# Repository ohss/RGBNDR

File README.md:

# RGBNDR

RGBNDR is a video synthesiser made by circuit bending a VGA test generator. Inspired by [CHA/V by Jonas Bers](https://jonasbers.com/chav/).

RGBNDR is currently a set of two PCB:s. A board for circuit bending a VGA signal and a board for generating nice signals for bending video. It's a modular design so new boards can be easily added later.

Here's some instructions about how to build one. Schematics, eagle files and gerbers for manufacturing can be found form [https://github.com/ohss/RGBNDR](https://github.com/ohss/RGBNDR)

You can find some examples about what you can do with one on Instagram: [https://www.instagram.com/explore/tags/rgbndr/](https://www.instagram.com/explore/tags/rgbndr/) or you can check out the video below:

# Build it!

You will need to build two boards: RGBNDR board and Modulator board:

Here's a RGBNDR board hooked up to two modulator boards:

Here's a quick tip on how to solder:

## Building RGBNDR (board with VGA test generator)

Here's what you'll need:

| Num | Part | Val | Comment | Link |
|-----|------|-----|---------|------|
|2x1|Male pin header||||			
|3x2|Male pin header||||			
|1x4|Female pin header|90° angle|||
|1|Led|3mm|||
|2|Pushbutton|MOMENTARY-SWITCH-SPST-PTH-6.0MM|||
|5|Slide switch|SLIDE SWITCH 1P2T THROUGH HOLE 0.5A 50VDC||https://www.taydaelectronics.com/slide-switch-1p2t-through-hole-0-5a-50vdc-2713.html|
|3|Ceramic capacitor|0.1uF (104)|Try out different values||
|3|Electrolytic capacitor|10uF|Try out different values. Remember polarity!||
|3|Potentiometer|10k|||
|1|Diode|1N4004|||
|3|Jumper wire||PCB has places for 1N4148 diodes. Use jumpers instead.||
|2|Resistor|1k|||
|1|Transistor|2N2222|Check polarity||
|1|Power Jack||V2 revision has a mistace on power. It's cCenter negative NOT center positive ||	
|3|Mono 3.5mm jack|Thonkiconn|Optional|https://www.thonk.co.uk/shop/3-5mm-jacks/|		

Start with adding caps to the bottom side. Remember to check polarity on electrolytic caps!

Use cap legs that you just cut out as jumpers. You'll need three. On the board there is three spots for 1N4148 diode. Use the jumpers instead.

Add two 1k resistors and 1N4004 diode. Remember to check diode polarity!

Next one is a bit tricky. You'll need to solder header pins to the board. I like to place the header pins on the board, put a piece on cardboard on top of the pins and then flip the whole thing over with the cardboard keeping the pins where they should be. Usually they fall all over the place.

Then: pushbuttons, transistor (match the flat side to the flat line on the board ) and led. Long leg goes to +.

Add female angle header for connecting with other board. Use a helping hand to get the angle header high enough:

Add (in this order): 5 slide switches, power connector, three 3.5mm mono jacks, three 10k potentiometers. For pots and slide switches it's ok to solder only the three middle pins.

Solder wires from the test gen board to the RGBNDR board.

Done!

## Building modulator board

Here's what you'll need:

| Num | Part | Val | Comment | Link |
|-----|------|-----|---------|------|
|11x1|Male pin header||||			
|5x2|Male pin header||||			
|1x4|Male pin header|90° angle|||
|4|LDR||Optional||
|13|Slide switch|SLIDE SWITCH 1P2T THROUGH HOLE 0.5A 50VDC|If you don't use LDRs, replace switch with jumper|https://www.taydaelectronics.com/slide-switch-1p2t-through-hole-0-5a-50vdc-2713.html|
|1|Ceramic capacitor|22pF||||
|1|Ceramic capacitor|0.001uF (102)|||
|2|Ceramic capacitor|0.01uF (103)|||
|5|Ceramic capacitor|0.1uF (104)|||
|2|Electrolytic capacitor|100uF|Remember polarity!||
|1|Electrolytic capacitor|10uF|Remember polarity!||
|1|Electrolytic capacitor|1uF|Remember polarity!||
|6|Potentiometer|100k|||
|1|Resistor|20k|||
|5|Resistor|100R|||
|1|IC|40106|||
|1|IC|4046|||
|1|IC|4070|||

Start with the flattest parts so that soldering is as easy as possible. So:

1. Resistors
2. ICs
3. Header pins
4. Caps
5. Switches
6. LDRs
7. Pots

Few tips:

Use IC sockets and align them correctly. I made a mistake on the photo:

You can chose what ever values for oscillator caps you want. Together with a potentiometer these will define frequency for an oscillator. For each oscillator you can pick big and small cap and change between those with a switch.

My setup is like this but try your own values!

|     |OSC 1|OSC 2|OSC 3|OSC 4|4046 MOD|
|-----|-----|-----|-----|-----|--------|
|SMALL|10nF|0.1nF|0.01nF|0.001nf| - |
| BIG |100nF|1nF|0.1nF|0.01nF|100nF|

I put the big caps on the bottom side.

After some soldering it should look more or less like this:

Hook it up with RGBNDR and that's it!

Later you can make a box for it. Here's an older version with jacks:

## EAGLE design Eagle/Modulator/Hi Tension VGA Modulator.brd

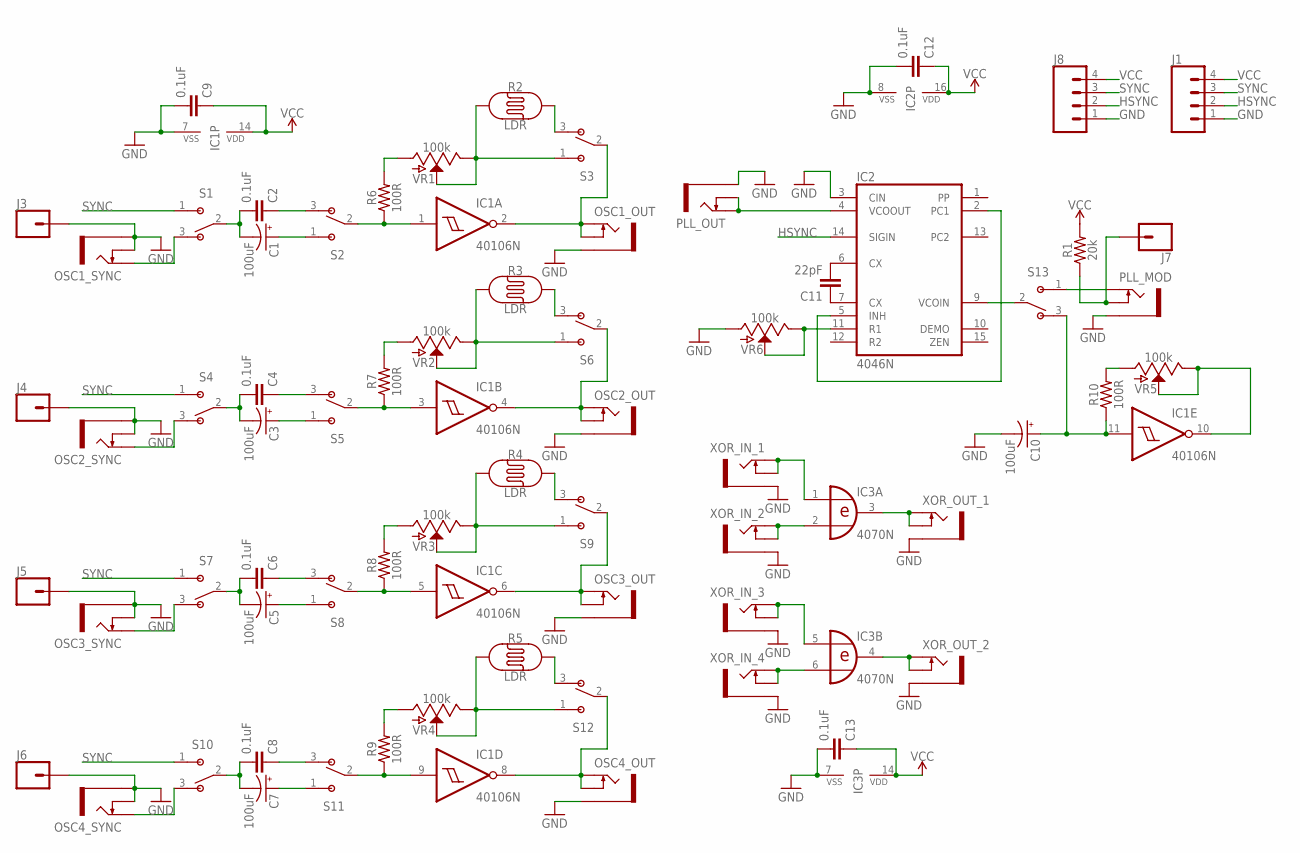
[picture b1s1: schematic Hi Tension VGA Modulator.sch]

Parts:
C1, C3, C5, C7, C10: 100uF; CPOL-RADIAL-2.5MM-6.5MM
C2, C4, C6, C8, C9, C12, C13: 0.1uF; C025-025X050
C11: 22pF; CAP-PTH-2.54
IC1: 40106N; DIL14
IC2: 4046N; DIL16
IC3: 4070N; DIL14
J1, J8: CONN_04; 1X04
J3, J4, J5, J6, J7: CONN_01PTH_NO_SILK_YES_STOP; 1X01_NO_SILK
OSC1_OUT, OSC1_SYNC, OSC2_OUT, OSC2_SYNC, OSC3_OUT, OSC3_SYNC, OSC4_OUT, OSC4_SYNC: THONKICONNNEW; WQP-PJ301M-12_JACK
PLL_MOD: THONKICONNNEW; WQP-PJ301M-12_JACK
PLL_OUT: THONKICONNNEW; WQP-PJ301M-12_JACK
R1: 20k; AXIAL-0.3
R2, R3, R4, R5: LDR; PHOTOCELL
R6, R7, R8, R9, R10: 100R; AXIAL-0.3
S1, S2, S3, S4, S5, S6, S7, S8, S9, S10, S11, S12, S13: OS102011MS2QN1; SW_OS102011MS2QN1
VR1, VR2, VR3, VR4, VR5, VR6: 100k; POT-PTH-ALPS
XOR_IN_1, XOR_IN_2, XOR_IN_3, XOR_IN_4: THONKICONNNEW; WQP-PJ301M-12_JACK
XOR_OUT_1, XOR_OUT_2: THONKICONNNEW; WQP-PJ301M-12_JACK

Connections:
GND: C9.2, C10.2 (-), C12.2, C13.2, IC1.7 (VSS), IC2.3 (CIN), IC2.8 (VSS), IC3.7 (VSS), J1.1, J3.1, J4.1, J5.1, J6.1, J8.1, OSC1_OUT.P$3_SLEEVE (SLEEVE), OSC1_SYNC.P$2_SWITCH (SWITCH), OSC1_SYNC.P$3_SLEEVE (SLEEVE), OSC2_OUT.P$3_SLEEVE (SLEEVE), OSC2_SYNC.P$2_SWITCH (SWITCH), OSC2_SYNC.P$3_SLEEVE (SLEEVE), OSC3_OUT.P$3_SLEEVE (SLEEVE), OSC3_SYNC.P$2_SWITCH (SWITCH), OSC3_SYNC.P$3_SLEEVE (SLEEVE), OSC4_OUT.P$3_SLEEVE (SLEEVE), OSC4_SYNC.P$2_SWITCH (SWITCH), OSC4_SYNC.P$3_SLEEVE (SLEEVE), PLL_MOD.P$3_SLEEVE (SLEEVE), PLL_OUT.P$3_SLEEVE (SLEEVE), VR6.P$3 (A), XOR_IN_1.P$3_SLEEVE (SLEEVE), XOR_IN_2.P$3_SLEEVE (SLEEVE), XOR_IN_3.P$3_SLEEVE (SLEEVE), XOR_IN_4.P$3_SLEEVE (SLEEVE), XOR_OUT_1.P$3_SLEEVE (SLEEVE), XOR_OUT_2.P$3_SLEEVE (SLEEVE)
HSYNC: IC2.14 (SIGIN), J1.2, J8.2
unnamed: OSC1_SYNC.P$1_TIP (TIP), S1.3
unnamed: C1.2 (-), C2.2, S1.2
unnamed: C2.1, S2.3
unnamed: C1.1 (+), S2.1
unnamed: IC1.1 (I), R6.P$1 (1), S2.2
unnamed: R10.P$2 (2), VR5.P$3 (A)
unnamed: R2.1, S3.1, VR1.P$1 (E), VR1.P$2 (S)
unnamed: IC1.2 (O), OSC1_OUT.P$1_TIP (TIP), OSC1_OUT.P$2_SWITCH (SWITCH), S3.2
unnamed: OSC2_SYNC.P$1_TIP (TIP), S4.3
unnamed: C3.2 (-), C4.2, S4.2
unnamed: C3.1 (+), S5.1
unnamed: IC1.3 (I), R7.P$1 (1), S5.2
unnamed: R2.2, S3.3
unnamed: IC1.4 (O), OSC2_OUT.P$1_TIP (TIP), OSC2_OUT.P$2_SWITCH (SWITCH), S6.2
unnamed: C4.1, S5.3
unnamed: OSC3_SYNC.P$1_TIP (TIP), S7.3
unnamed: C5.2 (-), C6.2, S7.2
unnamed: C5.1 (+), S8.1
unnamed: IC1.5 (I), R8.P$1 (1), S8.2
unnamed: R3.2, S6.3
unnamed: R5.2, S12.3
unnamed: IC1.6 (O), OSC3_OUT.P$1_TIP (TIP), OSC3_OUT.P$2_SWITCH (SWITCH), S9.2
unnamed: C6.1, S8.3
unnamed: OSC4_SYNC.P$1_TIP (TIP), S10.3
unnamed: C7.2 (-), C8.2, S10.2
unnamed: C8.1, S11.3
unnamed: IC1.9 (I), R9.P$1 (1), S11.2
unnamed: R4.1, S9.1, VR3.P$1 (E), VR3.P$2 (S)
unnamed: IC1.8 (O), OSC4_OUT.P$1_TIP (TIP), OSC4_OUT.P$2_SWITCH (SWITCH), S12.2
unnamed: C7.1 (+), S11.1
unnamed: C11.1, IC2.7 (CX)
unnamed: C11.2, IC2.6 (CX)
unnamed: IC2.9 (VCOIN), S13.2
unnamed: PLL_MOD.P$1_TIP (TIP), S13.1
unnamed: IC2.2 (PC1), IC2.5 (INH)
unnamed: IC2.4 (VCOOUT), PLL_OUT.P$1_TIP (TIP), PLL_OUT.P$2_SWITCH (SWITCH)
unnamed: J7.1, PLL_MOD.P$2_SWITCH (SWITCH), R1.P$1 (1)
unnamed: C10.1 (+), IC1.11 (I), R10.P$1 (1), S13.3
unnamed: IC1.10 (O), VR5.P$1 (E), VR5.P$2 (S)
unnamed: IC3.5 (I0), XOR_IN_3.P$1_TIP (TIP), XOR_IN_3.P$2_SWITCH (SWITCH)
unnamed: IC2.11 (R1), VR6.P$1 (E), VR6.P$2 (S)
unnamed: IC3.1 (I0), XOR_IN_1.P$1_TIP (TIP), XOR_IN_1.P$2_SWITCH (SWITCH)
unnamed: IC3.2 (I1), XOR_IN_2.P$1_TIP (TIP), XOR_IN_2.P$2_SWITCH (SWITCH)
unnamed: IC3.6 (I1), XOR_IN_4.P$1_TIP (TIP), XOR_IN_4.P$2_SWITCH (SWITCH)
unnamed: IC3.3 (O), XOR_OUT_1.P$1_TIP (TIP), XOR_OUT_1.P$2_SWITCH (SWITCH)
unnamed: IC3.4 (O), XOR_OUT_2.P$1_TIP (TIP), XOR_OUT_2.P$2_SWITCH (SWITCH)
unnamed: R4.2, S9.3
unnamed: R3.1, S6.1, VR2.P$1 (E), VR2.P$2 (S)
unnamed: R5.1, S12.1, VR4.P$1 (E), VR4.P$2 (S)
unnamed: R6.P$2 (2), VR1.P$3 (A)
unnamed: R7.P$2 (2), VR2.P$3 (A)
unnamed: R8.P$2 (2), VR3.P$3 (A)
unnamed: R9.P$2 (2), VR4.P$3 (A)
SYNC: J1.3, J8.3, S1.1, S4.1, S7.1, S10.1
VCC: C9.1, C12.1, C13.1, IC1.14 (VDD), IC2.16 (VDD), IC3.14 (VDD), J1.4, J8.4, R1.P$2 (2)

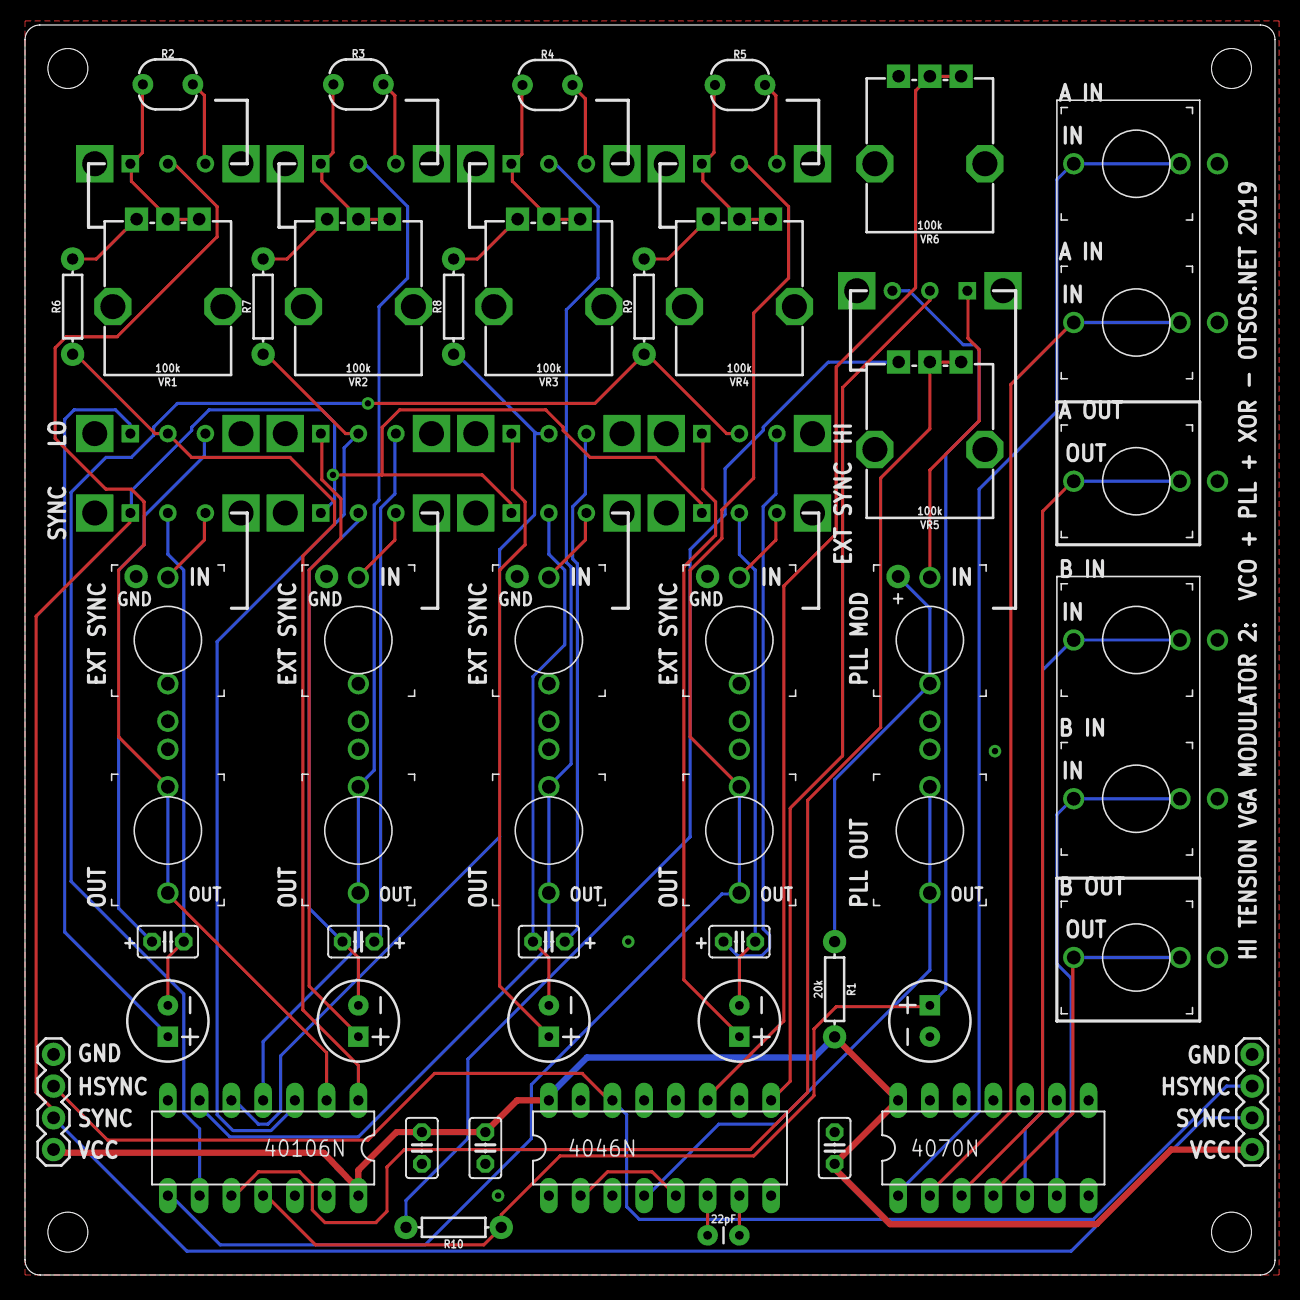
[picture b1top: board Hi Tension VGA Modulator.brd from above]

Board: 2 copper layers, 100.0 x 100.0 mm, 72 parts (0 on the bottom side), 57 nets.

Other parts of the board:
U$1, U$2, U$3, U$4: MOUNTING_HOLE

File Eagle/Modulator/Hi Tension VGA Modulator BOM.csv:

"Qty";"Value";"Device";"Package";"Parts";"Description";"AVAILABILITY";"DESCRIPTION";"MF";"MP";"PACKAGE";"PRICE";"PROD_ID";"SF_ID";"SF_SKU";"SPICEPREFIX";"VALUE";
"5";"";"CONN_01PTH_NO_SILK_YES_STOP";"1X01_NO_SILK";"J3, J4, J5, J6, J7";"Single connection point. Often used as Generic Header-pin footprint for 0.1 inch spaced/style header connections";"";"";"";"";"";"";"";"";"";"";"";
"2";"";"CONN_04";"1X04";"J1, J8";"Multi connection point. Often used as Generic Header-pin footprint for 0.1 inch spaced/style header connections";"";"";"";"";"";"";"CONN-09696";"";"";"";"";
"13";"";"OS102011MS2QN1";"SW_OS102011MS2QN1";"S1, S2, S3, S4, S5, S6, S7, S8, S9, S10, S11, S12, S13";"Switch Slide ON ON SPDT Top Slide 0.1A 12VDC 10000Cycles PC Pins Thru-Hole Bulk";"Unavailable";" Switch Slide ON ON SPDT Top Slide 0.1A 12VDC 10000Cycles PC Pins Thru-Hole Bulk ";"C&K";"OS102011MS2QN1";"DO-201 C&amp";"K Components";"None";"";"";"";"";
"7";"0.1uF";"C-EU025-025X050";"C025-025X050";"C2, C4, C6, C8, C9, C12, C13";"CAPACITOR, European symbol";"";"";"";"";"";"";"";"";"";"C";"";
"5";"100R";"1KOHM-HORIZ-1/4W-1%";"AXIAL-0.3";"R6, R7, R8, R9, R10";"1kΩ resistor";"";"";"";"";"";"";"RES-12182";"";"";"";"1k";
"6";"100k";"POTENTIOMETER-PTH-9MM-1/20W-20%";"POT-PTH-ALPS";"VR1, VR2, VR3, VR4, VR5, VR6";"Potentiometer (Pot)";"";"";"";"";"";"";"RES-09177";"";"COM-09288";"";"10k";
"5";"100uF";"100UF-POLAR-RADIAL-2.5MM-25V-20%";"CPOL-RADIAL-2.5MM-6.5MM";"C1, C3, C5, C7, C10";"100µF polarized capacitors";"";"";"";"";"";"";"CAP-08439";"";"";"";"100uF";
"1";"20k";"1KOHM-HORIZ-1/4W-1%";"AXIAL-0.3";"R1";"1kΩ resistor";"";"";"";"";"";"";"RES-12182";"";"";"";"1k";
"1";"22pF";"22PF-PTH-2.54MM-200V-5%";"CAP-PTH-2.54";"C11";"22pF ceramic capacitors";"";"";"";"";"";"";"CAP-09128";"";"";"";"22pF";
"1";"40106N";"40106N";"DIL14";"IC1";"Hex SCHMITT TRIGGER";"";"";"";"";"";"";"";"";"";"";"";
"1";"4046N";"4046N";"DIL16";"IC2";"Micropower PLL";"";"";"";"";"";"";"";"";"";"";"";
"1";"4070N";"4070N";"DIL14";"IC3";"Quad 2-input XOR";"";"";"";"";"";"";"";"";"";"";"";
"4";"LDR";"PHOTOCELLPTH";"PHOTOCELL";"R2, R3, R4, R5";"Photocell (Photodetector, Photo Resistor, CdS)";"";"";"";"";"";"";"COMP-09129";"SEN-09088";"";"";"";
"16";"THONKICONNNEW";"THONKICONNNEW";"WQP-PJ301M-12_JACK";"OSC1_OUT, OSC1_SYNC, OSC2_OUT, OSC2_SYNC, OSC3_OUT, OSC3_SYNC, OSC4_OUT, OSC4_SYNC, PLL_MOD, PLL_OUT, XOR_IN_1, XOR_IN_2, XOR_IN_3, XOR_IN_4, XOR_OUT_1, XOR_OUT_2";"3.5mm socket for Eurorack modular synths";"";"";"";"";"";"";"";"";"";"";"";

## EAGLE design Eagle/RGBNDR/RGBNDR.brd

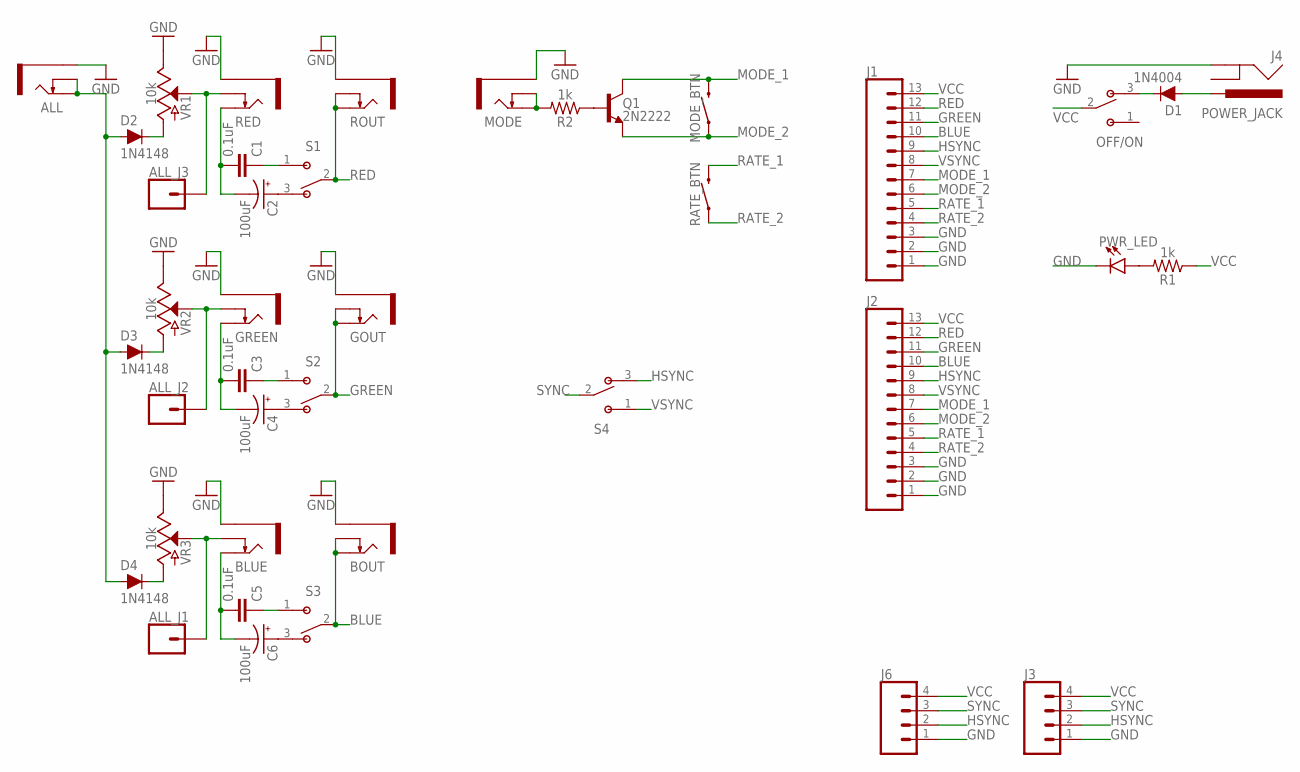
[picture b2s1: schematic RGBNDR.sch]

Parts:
ALL: THONKICONNNEW; WQP-PJ301M-12_JACK
ALL_J1, ALL_J2, ALL_J3: CONN_01PTH_NO_SILK_YES_STOP; 1X01_NO_SILK
BLUE: THONKICONNNEW; WQP-PJ301M-12_JACK
BOUT: THONKICONNNEW; WQP-PJ301M-12_JACK
C1, C3, C5: 0.1uF; C025-025X050
C2, C4, C6: 100uF; CPOL-RADIAL-2.5MM-6.5MM
D1: 1N4004; DIODE-1N4001
D2, D3, D4: 1N4148; DIODE-1N4148
GOUT: THONKICONNNEW; WQP-PJ301M-12_JACK
GREEN: THONKICONNNEW; WQP-PJ301M-12_JACK
J1, J2: CONN_13LONGPADS; 1X13-LONGPADS
J3, J6: CONN_04; 1X04
J4: POWER_JACK; POWER_JACK_PTH
MODE: THONKICONNNEW; WQP-PJ301M-12_JACK
MODE_BTN: MOMENTARY-SWITCH-SPST-PTH-6.0MM; TACTILE_SWITCH_PTH_6.0MM
OFF/ON: OS102011MS2QN1; SW_OS102011MS2QN1
PWR_LED: LED3MM; LED_3MM
Q1: 2N2222; TO-92
R1, R2: 1k; AXIAL-0.3
RATE_BTN: MOMENTARY-SWITCH-SPST-PTH-6.0MM; TACTILE_SWITCH_PTH_6.0MM
RED: THONKICONNNEW; WQP-PJ301M-12_JACK
ROUT: THONKICONNNEW; WQP-PJ301M-12_JACK
S1, S2, S3, S4: OS102011MS2QN1; SW_OS102011MS2QN1
VR1, VR2, VR3: 10k; POT-PTH-ALPS

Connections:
BLUE: BOUT.P$1_TIP (TIP), BOUT.P$2_SWITCH (SWITCH), J1.10, J2.10, S3.2
GND: ALL.P$3_SLEEVE (SLEEVE), BLUE.P$3_SLEEVE (SLEEVE), BOUT.P$3_SLEEVE (SLEEVE), GOUT.P$3_SLEEVE (SLEEVE), GREEN.P$3_SLEEVE (SLEEVE), J1.1, J1.2, J1.3, J2.1, J2.2, J2.3, J3.1, J4.GND, J6.1, MODE.P$3_SLEEVE (SLEEVE), PWR_LED.K (C), RED.P$3_SLEEVE (SLEEVE), ROUT.P$3_SLEEVE (SLEEVE), VR1.P$1 (E), VR2.P$1 (E), VR3.P$1 (E)
GREEN: GOUT.P$1_TIP (TIP), GOUT.P$2_SWITCH (SWITCH), J1.11, J2.11, S2.2
HSYNC: J1.9, J2.9, J3.2, J6.2, S4.3
MODE_1: J1.7, J2.7, MODE_BTN.3 (2), Q1.3 (C)
MODE_2: J1.6, J2.6, MODE_BTN.1, Q1.1 (E)
unnamed: ALL_J3.1, RED.P$2_SWITCH (SWITCH), VR1.P$2 (S)
unnamed: ALL_J2.1, GREEN.P$2_SWITCH (SWITCH), VR2.P$2 (S)
unnamed: ALL_J1.1, BLUE.P$2_SWITCH (SWITCH), VR3.P$2 (S)
unnamed: D1.A, J4.PWR
unnamed: D1.C, OFF/ON.3
unnamed: D2.C, VR1.P$3 (A)
unnamed: D3.C, VR2.P$3 (A)
unnamed: D4.C, VR3.P$3 (A)
unnamed: PWR_LED.A, R1.P$2 (2)
unnamed: MODE.P$1_TIP (TIP), MODE.P$2_SWITCH (SWITCH), R2.P$2 (2)
unnamed: C1.1, S1.1
unnamed: C2.1 (+), S1.3
unnamed: C1.2, C2.2 (-), RED.P$1_TIP (TIP)
unnamed: Q1.2 (B), R2.P$1 (1)
unnamed: C3.1, S2.1
unnamed: C4.1 (+), S2.3
unnamed: C3.2, C4.2 (-), GREEN.P$1_TIP (TIP)
unnamed: ALL.P$1_TIP (TIP), ALL.P$2_SWITCH (SWITCH), D2.A, D3.A, D4.A
unnamed: C5.1, S3.1
unnamed: C6.1 (+), S3.3
unnamed: BLUE.P$1_TIP (TIP), C5.2, C6.2 (-)
RATE_1: J1.5, J2.5, RATE_BTN.3 (2)
RATE_2: J1.4, J2.4, RATE_BTN.1
RED: J1.12, J2.12, ROUT.P$1_TIP (TIP), ROUT.P$2_SWITCH (SWITCH), S1.2
SYNC: J3.3, J6.3, S4.2
VCC: J1.13, J2.13, J3.4, J6.4, OFF/ON.2, R1.P$1 (1)
VSYNC: J1.8, J2.8, S4.1

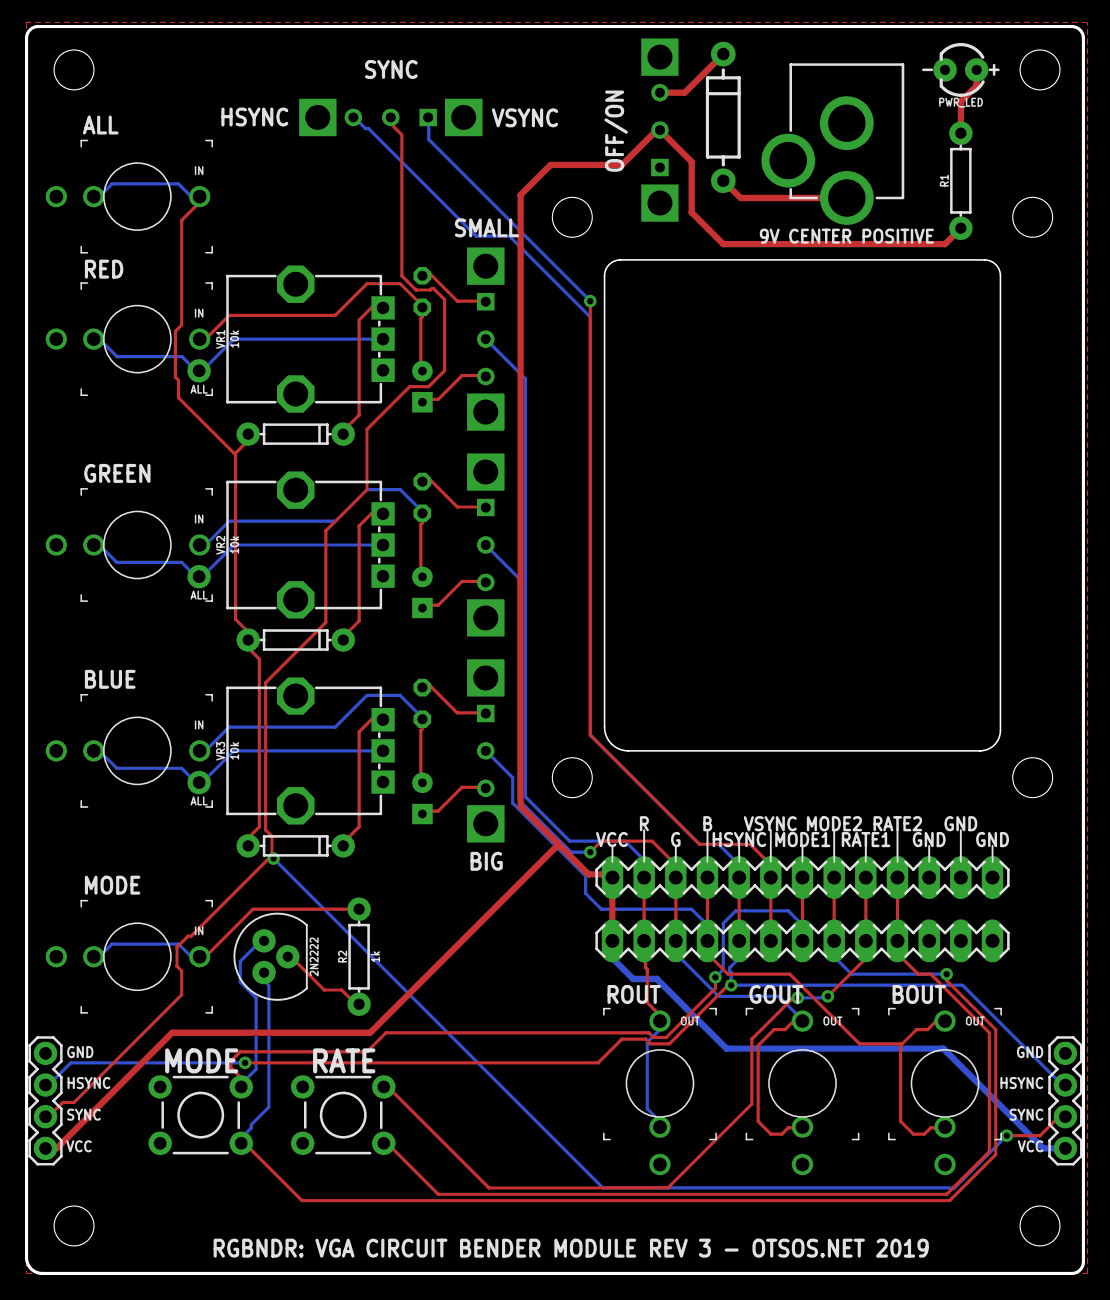
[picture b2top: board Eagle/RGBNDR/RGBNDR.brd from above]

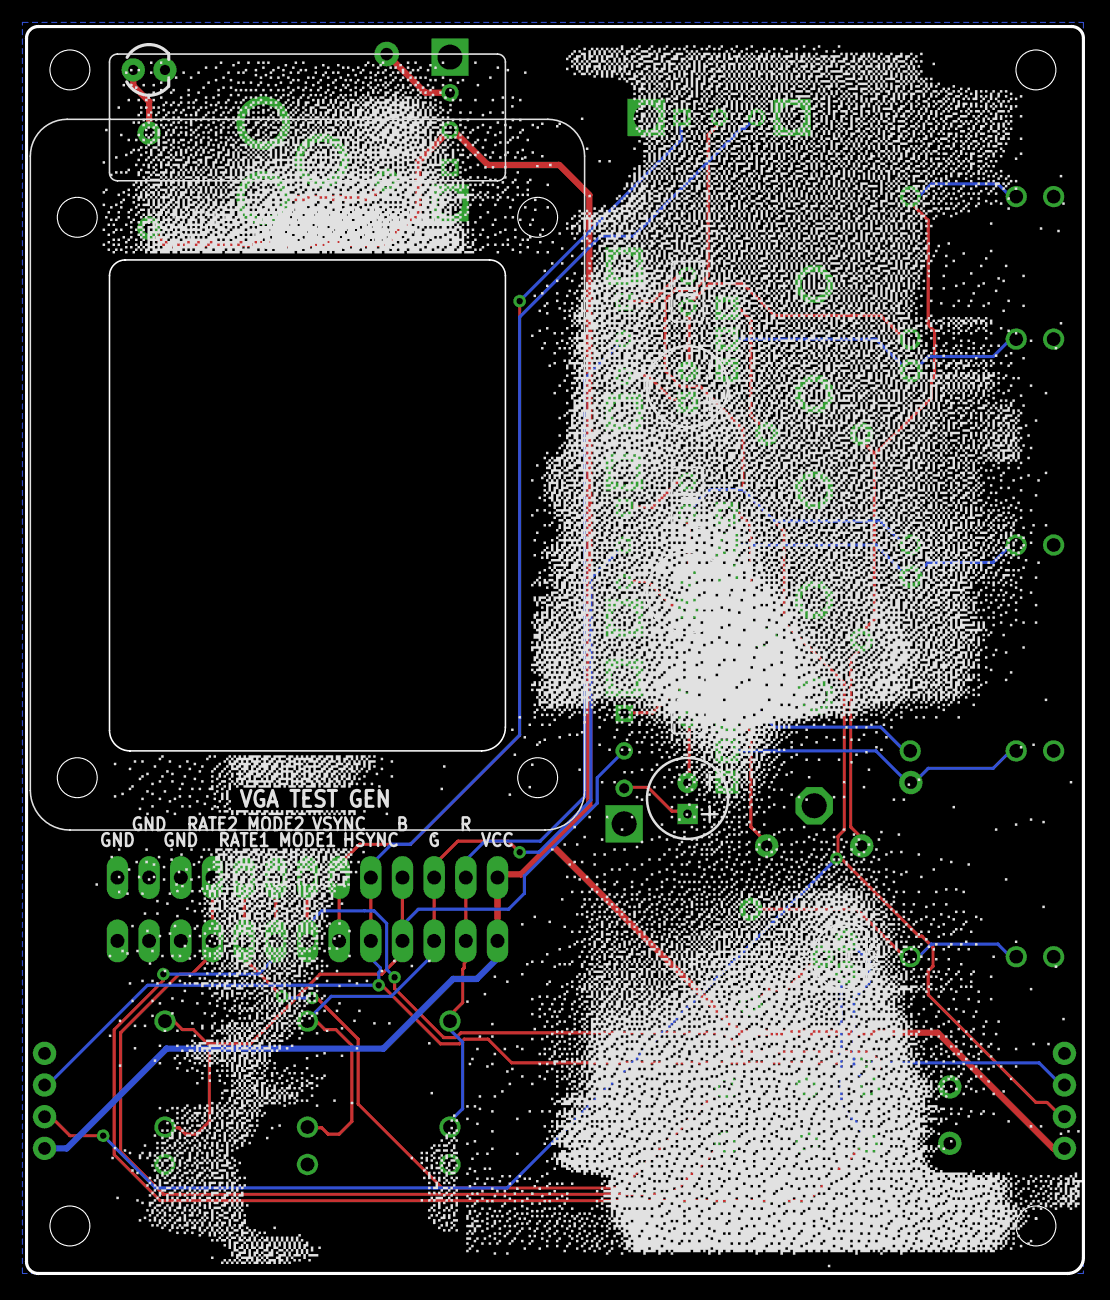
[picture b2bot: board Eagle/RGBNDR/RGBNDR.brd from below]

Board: 2 copper layers, 84.8 x 100.0 mm, 45 parts (8 on the bottom side), 33 nets.

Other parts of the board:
U$1: VGATESTGEN
U$2, U$3, U$4, U$5: MOUNTING_HOLE

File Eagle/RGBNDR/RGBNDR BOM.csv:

"Qty";"Value";"Device";"Package";"Parts";"Description";"AVAILABILITY";"DESCRIPTION";"MF";"MP";"PACKAGE";"PRICE";"PROD_ID";"SF_SKU";"SPICEPREFIX";"VALUE";
"3";"";"CONN_01PTH_NO_SILK_YES_STOP";"1X01_NO_SILK";"ALL_J1, ALL_J2, ALL_J3";"Single connection point. Often used as Generic Header-pin footprint for 0.1 inch spaced/style header connections";"";"";"";"";"";"";"";"";"";"";
"2";"";"CONN_04";"1X04";"J3, J6";"Multi connection point. Often used as Generic Header-pin footprint for 0.1 inch spaced/style header connections";"";"";"";"";"";"";"CONN-09696";"";"";"";
"2";"";"CONN_13LONGPADS";"1X13-LONGPADS";"J1, J2";"Multi connection point. Often used as Generic Header-pin footprint for 0.1 inch spaced/style header connections";"";"";"";"";"";"";"";"";"";"";
"1";"";"LED3MM";"LED_3MM";"PWR_LED";"LED (Generic)";"";"";"";"";"";"";"DIO-08794";"";"";"";
"2";"";"MOMENTARY-SWITCH-SPST-PTH-6.0MM";"TACTILE_SWITCH_PTH_6.0MM";"MODE_BTN, RATE_BTN";"Momentary Switch (Pushbutton) - SPST";"";"";"";"";"";"";" SWCH-08441";"COM-00097";"";"";
"5";"";"OS102011MS2QN1";"SW_OS102011MS2QN1";"OFF/ON, S1, S2, S3, S4";"Switch Slide ON ON SPDT Top Slide 0.1A 12VDC 10000Cycles PC Pins Thru-Hole Bulk";"Unavailable";" Switch Slide ON ON SPDT Top Slide 0.1A 12VDC 10000Cycles PC Pins Thru-Hole Bulk ";"C&K";"OS102011MS2QN1";"DO-201 C&amp";"K Components";"None";"";"";"";
"3";"0.1uF";"C-EU025-025X050";"C025-025X050";"C1, C3, C5";"CAPACITOR, European symbol";"";"";"";"";"";"";"";"";"C";"";
"3";"100uF";"100UF-POLAR-RADIAL-2.5MM-25V-20%";"CPOL-RADIAL-2.5MM-6.5MM";"C2, C4, C6";"100µF polarized capacitors";"";"";"";"";"";"";"CAP-08439";"";"";"100uF";
"3";"10k";"POTENTIOMETER-PTH-9MM-1/20W-20%";"POT-PTH-ALPS";"VR1, VR2, VR3";"Potentiometer (Pot)";"";"";"";"";"";"";"RES-09177";"COM-09288";"";"10k";
"1";"1N4004";"DIODE-PTH";"DIODE-1N4001";"D1";"Diode";"";"";"";"";"";"";"DIO-09176";"";"";"1A/50V/1.1V";
"3";"1N4148";"DIODE-1N4148";"DIODE-1N4148";"D2, D3, D4";"Diode";"";"";"";"";"";"";"DIO-08378";"";"";"200mA/100V/1V";
"2";"1k";"1KOHM-HORIZ-1/4W-1%";"AXIAL-0.3";"R1, R2";"1kΩ resistor";"";"";"";"";"";"";"RES-12182";"";"";"1k";
"1";"2N2222";"TRANS_NPN-2N3904";"TO-92";"Q1";"NPN transistor";"";"";"";"";"";"";"TRANS-08447";"";"";"200mA/40V";
"1";"POWER_JACK";"POWER_JACK";"POWER_JACK_PTH";"J4";"Power Jack Connector";"";"";"";"";"";"";"CONN-08197";"";"";"";
"8";"THONKICONNNEW";"THONKICONNNEW";"WQP-PJ301M-12_JACK";"ALL, BLUE, BOUT, GOUT, GREEN, MODE, RED, ROUT";"3.5mm socket for Eurorack modular synths";"";"";"";"";"";"";"";"";"";"";

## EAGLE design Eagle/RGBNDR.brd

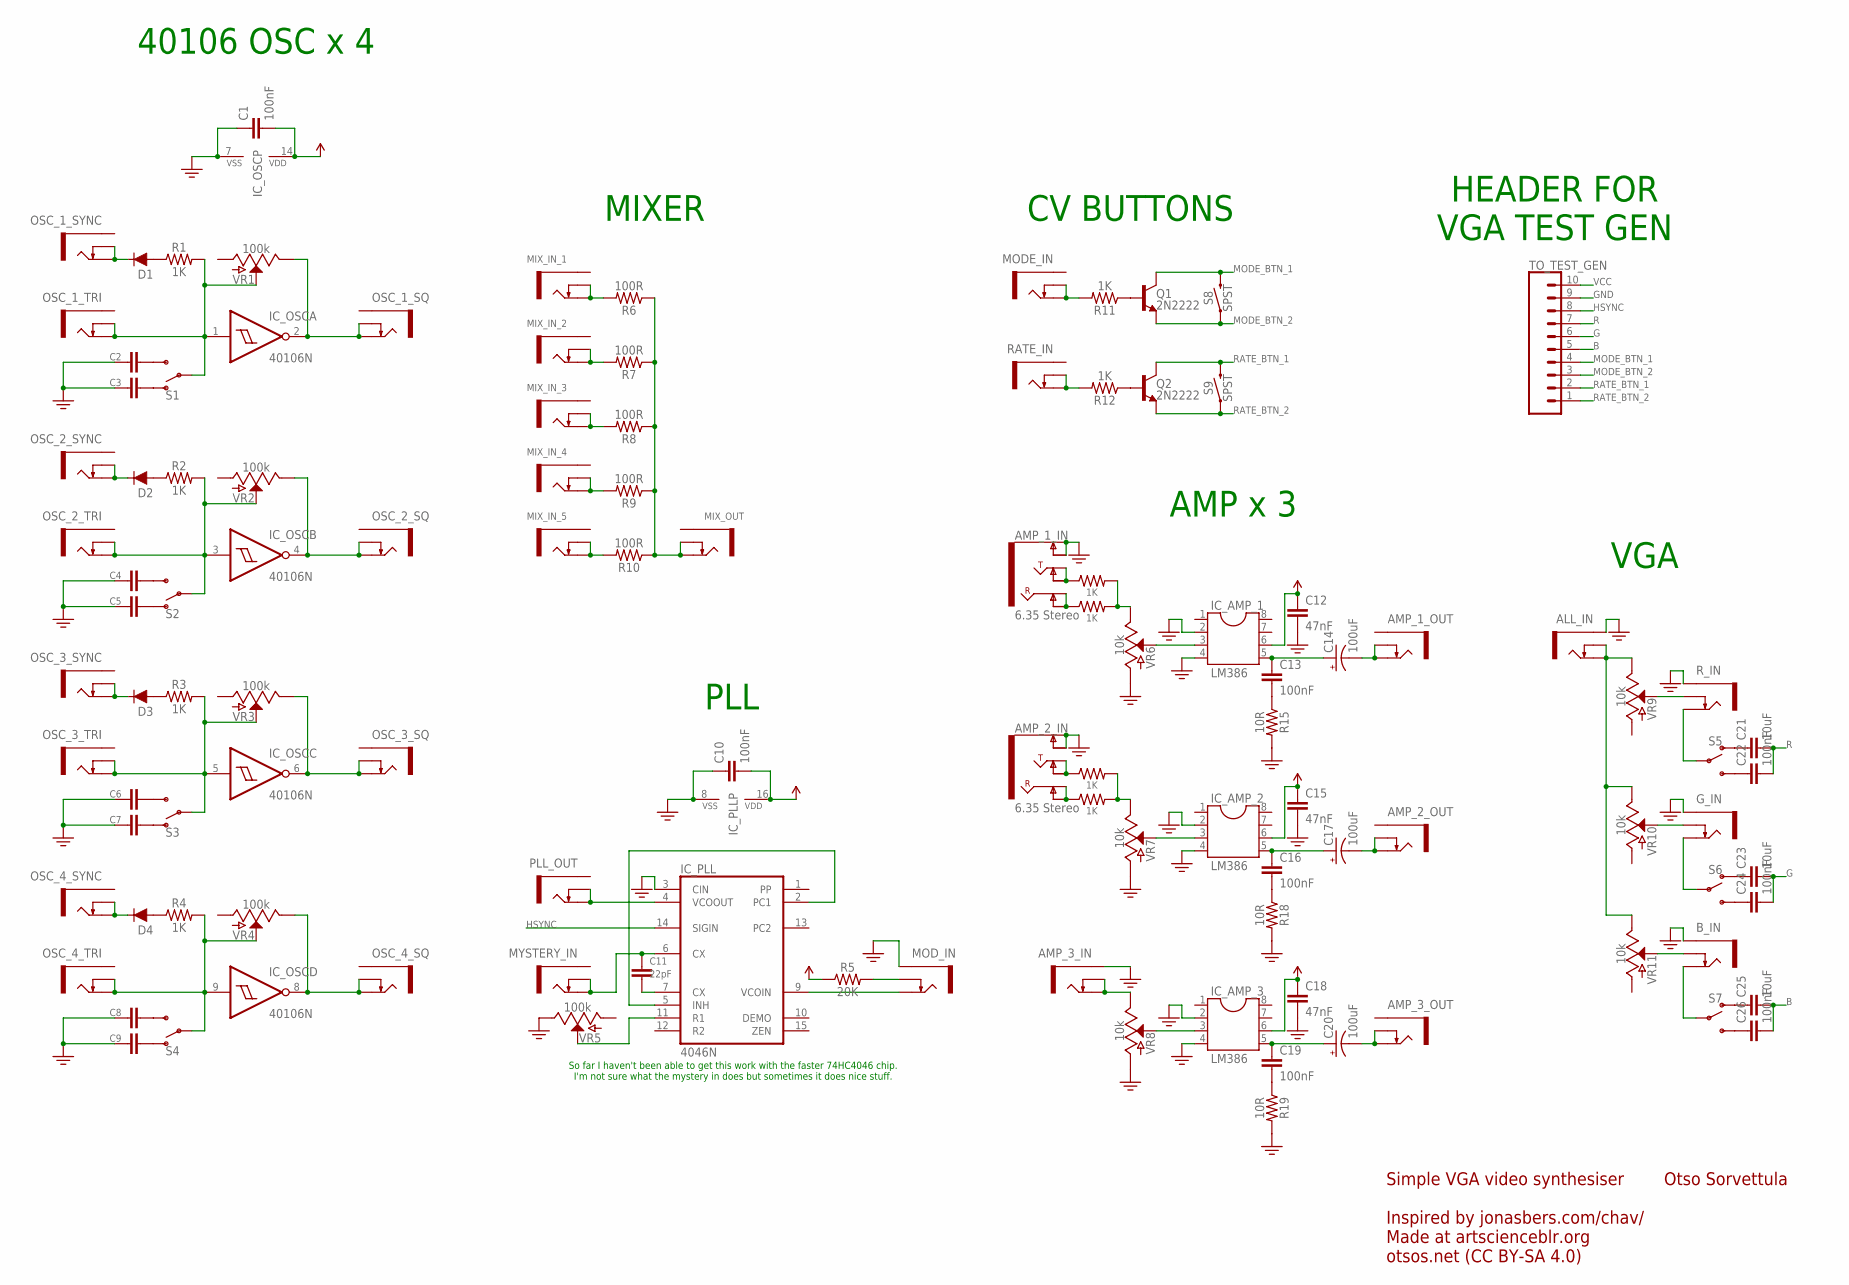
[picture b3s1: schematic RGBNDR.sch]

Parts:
ALL_IN: WQP-PJ301M-12_JACK
AMP_1_IN, AMP_2_IN: 6.35 Stereo; AUDIO_JACK_0.25"_TRS_PTH_RA
AMP_1_OUT, AMP_2_OUT, AMP_3_IN, AMP_3_OUT: WQP-PJ301M-12_JACK
B_IN: WQP-PJ301M-12_JACK
C1, C10, C13, C16, C19, C22, C24, C26: 100nF; CAP-PTH-SMALL-KIT
C2, C3, C4, C5, C6, C7, C8, C9: 0.1UF-KIT-EZ-50V-20%; CAP-PTH-SMALL-KIT
C11: 22pF; CAP-PTH-2.54
C12, C15, C18: 47nF; CAP-PTH-SMALL-KIT
C14, C17, C20: 100uF; CPOL-RADIAL-2.5MM-6.5MM
C21, C23, C25: 10uF; CAP-PTH-SMALL-KIT
D1, D2, D3, D4: DIODE-1N4148
G_IN: WQP-PJ301M-12_JACK
IC_AMP_1, IC_AMP_2, IC_AMP_3: LM386; DIL08
IC_OSC: 40106N; DIL14
IC_PLL: 4046N; DIL16
MIX_IN_1, MIX_IN_2, MIX_IN_3, MIX_IN_4, MIX_IN_5: WQP-PJ301M-12_JACK
MIX_OUT: WQP-PJ301M-12_JACK
MODE_IN: WQP-PJ301M-12_JACK
MOD_IN: WQP-PJ301M-12_JACK
MYSTERY_IN: WQP-PJ301M-12_JACK
OSC_1_SQ, OSC_1_SYNC, OSC_1_TRI, OSC_2_SQ, OSC_2_SYNC, OSC_2_TRI, OSC_3_SQ, OSC_3_SYNC, OSC_3_TRI, OSC_4_SQ, OSC_4_SYNC, OSC_4_TRI: WQP-PJ301M-12_JACK
PLL_OUT: WQP-PJ301M-12_JACK
Q1, Q2: 2N2222; TO-92
R1, R2, R3, R4, R11, R12, R13, R14, R16, R17: 1K; AXIAL-0.3
R5: 20K; AXIAL-0.3
R6, R7, R8, R9, R10: 100R; AXIAL-0.3
R15, R18, R19: 10R; AXIAL-0.3
RATE_IN: WQP-PJ301M-12_JACK
R_IN: WQP-PJ301M-12_JACK
S1, S2, S3, S4, S5, S6, S7: SWITCH-SPDT-PTH-11.6X4.0MM-LOCK; SWITCH_SPDT_PTH_11.6X4.0MM_LOCK
S8, S9: SPST; TACTILE_SWITCH_PTH_6.0MM
TO_TEST_GEN: CONN_10"; 1X10
VR1, VR2, VR3, VR4, VR5: 100k; POT-PTH-ALPS-KIT
VR6, VR7, VR8, VR9, VR10, VR11: 10k; POT-PTH-ALPS-KIT

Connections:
B: C25.2, C26.2, TO_TEST_GEN.5
G: C23.2, C24.2, TO_TEST_GEN.6
GND: ALL_IN.P$1, AMP_1_IN.SLEEVE (EARTH), AMP_1_IN.SLEEVE-NORM (EARTH-NORM), AMP_2_IN.SLEEVE (EARTH), AMP_2_IN.SLEEVE-NORM (EARTH-NORM), AMP_3_IN.P$1, B_IN.P$1, C1.1, C2.2, C3.2, C4.2, C5.2, C6.2, C7.2, C8.2, C9.2, C10.1, C12.2, C15.2, C18.2, G_IN.P$1, IC_AMP_1.2, IC_AMP_1.4, IC_AMP_2.2, IC_AMP_2.4, IC_AMP_3.2, IC_AMP_3.4, IC_OSC.7 (VSS), IC_PLL.3 (CIN), IC_PLL.8 (VSS), MOD_IN.P$1, R15.P$2 (2), R18.P$2 (2), R19.P$2 (2), R_IN.P$1, TO_TEST_GEN.9, VR5.P$1 (E), VR6.P$3 (A), VR7.P$3 (A), VR8.P$3 (A)
HSYNC: IC_PLL.14 (SIGIN), TO_TEST_GEN.8
MODE_BTN_1: Q1.1 (C), S8.3 (2), TO_TEST_GEN.4
MODE_BTN_2: Q1.3 (E), S8.1, TO_TEST_GEN.3
unnamed: IC_PLL.2 (PC1), IC_PLL.5 (INH)
unnamed: C11.1, IC_PLL.6 (CX), MYSTERY_IN.P$2, MYSTERY_IN.P$3
unnamed: C11.2, IC_PLL.7 (CX)
unnamed: MIX_IN_1.P$2, MIX_IN_1.P$3, R6.P$2 (2)
unnamed: MIX_IN_2.P$2, MIX_IN_2.P$3, R7.P$2 (2)
unnamed: MIX_IN_3.P$2, MIX_IN_3.P$3, R8.P$2 (2)
unnamed: MIX_IN_4.P$2, MIX_IN_4.P$3, R9.P$2 (2)
unnamed: IC_AMP_1.3, VR6.P$2 (S)
unnamed: C13.2, R15.P$1 (1)
unnamed: MIX_IN_5.P$2, MIX_IN_5.P$3, R10.P$2 (2)
unnamed: MIX_OUT.P$2, MIX_OUT.P$3, R6.P$1 (1), R7.P$1 (1), R8.P$1 (1), R9.P$1 (1), R10.P$1 (1)
unnamed: C13.1, C14.1 (+), IC_AMP_1.5
unnamed: ALL_IN.P$2, ALL_IN.P$3, VR9.P$1 (E), VR10.P$1 (E), VR11.P$1 (E)
unnamed: D2.A, R2.P$1 (1)
unnamed: R_IN.P$3, VR9.P$2 (S)
unnamed: R_IN.P$2, S5.2
unnamed: IC_OSC.2 (O), OSC_1_SQ.P$2, OSC_1_SQ.P$3, VR1.P$1 (E)
unnamed: D2.C, OSC_2_SYNC.P$2, OSC_2_SYNC.P$3
unnamed: IC_OSC.4 (O), OSC_2_SQ.P$2, OSC_2_SQ.P$3, VR2.P$1 (E)
unnamed: IC_OSC.3 (I), OSC_2_TRI.P$2, OSC_2_TRI.P$3, R2.P$2 (2), S2.2, VR2.P$2 (S)
unnamed: C4.1, S2.3 (S)
unnamed: C22.1, S5.3 (S)
unnamed: C21.1, S5.1 (O)
unnamed: G_IN.P$3, VR10.P$2 (S)
unnamed: G_IN.P$2, S6.2
unnamed: C24.1, S6.3 (S)
unnamed: C23.1, S6.1 (O)
unnamed: R13.P$2 (2), R14.P$2 (2), VR6.P$1 (E)
unnamed: D1.C, OSC_1_SYNC.P$2, OSC_1_SYNC.P$3
unnamed: D1.A, R1.P$1 (1)
unnamed: IC_OSC.1 (I), OSC_1_TRI.P$2, OSC_1_TRI.P$3, R1.P$2 (2), S1.2, VR1.P$2 (S)
unnamed: C2.1, S1.3 (S)
unnamed: C3.1, S1.1 (O)
unnamed: C5.1, S2.1 (O)
unnamed: D3.A, R3.P$1 (1)
unnamed: D3.C, OSC_3_SYNC.P$2, OSC_3_SYNC.P$3
unnamed: IC_OSC.6 (O), OSC_3_SQ.P$2, OSC_3_SQ.P$3, VR3.P$1 (E)
unnamed: IC_OSC.5 (I), OSC_3_TRI.P$2, OSC_3_TRI.P$3, R3.P$2 (2), S3.2, VR3.P$2 (S)
unnamed: C6.1, S3.3 (S)
unnamed: C7.1, S3.1 (O)
unnamed: D4.A, R4.P$1 (1)
unnamed: D4.C, OSC_4_SYNC.P$2, OSC_4_SYNC.P$3
unnamed: IC_OSC.8 (O), OSC_4_SQ.P$2, OSC_4_SQ.P$3, VR4.P$1 (E)
unnamed: IC_OSC.9 (I), OSC_4_TRI.P$2, OSC_4_TRI.P$3, R4.P$2 (2), S4.2, VR4.P$2 (S)
unnamed: C8.1, S4.3 (S)
unnamed: C9.1, S4.1 (O)
unnamed: IC_PLL.11 (R1), VR5.P$2 (S)
unnamed: MOD_IN.P$3, R5.P$2 (2)
unnamed: IC_PLL.9 (VCOIN), MOD_IN.P$2
unnamed: AMP_1_IN.TIP, AMP_1_IN.TIP-NORM, R13.P$1 (1)
unnamed: AMP_1_IN.RING, AMP_1_IN.RING-NORM, R14.P$1 (1)
unnamed: AMP_1_OUT.P$2, AMP_1_OUT.P$3, C14.2 (-)
unnamed: IC_AMP_2.3, VR7.P$2 (S)
unnamed: C16.2, R18.P$1 (1)
unnamed: C16.1, C17.1 (+), IC_AMP_2.5
unnamed: AMP_2_IN.TIP, AMP_2_IN.TIP-NORM, R16.P$1 (1)
unnamed: AMP_2_IN.RING, AMP_2_IN.RING-NORM, R17.P$1 (1)
unnamed: R16.P$2 (2), R17.P$2 (2), VR7.P$1 (E)
unnamed: AMP_2_OUT.P$2, AMP_2_OUT.P$3, C17.2 (-)
unnamed: IC_AMP_3.3, VR8.P$2 (S)
unnamed: C19.2, R19.P$1 (1)
unnamed: C19.1, C20.1 (+), IC_AMP_3.5
unnamed: B_IN.P$3, VR11.P$2 (S)
unnamed: B_IN.P$2, S7.2
unnamed: AMP_3_IN.P$2, AMP_3_IN.P$3, VR8.P$1 (E)
unnamed: AMP_3_OUT.P$2, AMP_3_OUT.P$3, C20.2 (-)
unnamed: C26.1, S7.3 (S)
unnamed: C25.1, S7.1 (O)
unnamed: Q1.2 (B), R11.P$1 (1)
unnamed: MODE_IN.P$2, MODE_IN.P$3, R11.P$2 (2)
unnamed: Q2.2 (B), R12.P$1 (1)
unnamed: R12.P$2 (2), RATE_IN.P$2, RATE_IN.P$3
PLL_OUT: IC_PLL.4 (VCOOUT), PLL_OUT.P$2, PLL_OUT.P$3
R: C21.2, C22.2, TO_TEST_GEN.7
RATE_BTN_1: Q2.1 (C), S9.3 (2), TO_TEST_GEN.2
RATE_BTN_2: Q2.3 (E), S9.1, TO_TEST_GEN.1
VCC: C1.2, C10.2, C12.1, C15.1, C18.1, IC_AMP_1.6, IC_AMP_2.6, IC_AMP_3.6, IC_OSC.14 (VDD), IC_PLL.16 (VDD), R5.P$1 (1), TO_TEST_GEN.10

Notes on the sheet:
So far I haven't been able to get this work with the faster 74HC4046 chip. I'm not sure what the mystery in does but sometimes it does nice stuff.
Otso Sorvettula
Simple VGA video synthesiser Inspired by jonasbers.com/chav/ Made at artscienceblr.org otsos.net (CC BY-SA 4.0)
40106 OSC x 4
MIXER
PLL
CV BUTTONS
AMP x 3
VGA
HEADER FOR VGA TEST GEN

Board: 2 copper layers, 110 parts (0 on the bottom side), 83 nets, no tracks yet.

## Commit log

2018-03-07 Change image filenames
2018-03-07 add img folder
2018-03-07 move files around
2018-03-07 reset brd
2019-03-16 Fix filenames

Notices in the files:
parts and their libraries:
SparkFun-Capacitors: Licensing: Creative Commons ShareAlike 4.0 International - https://creativecommons.org/licenses/by-sa/4.0
